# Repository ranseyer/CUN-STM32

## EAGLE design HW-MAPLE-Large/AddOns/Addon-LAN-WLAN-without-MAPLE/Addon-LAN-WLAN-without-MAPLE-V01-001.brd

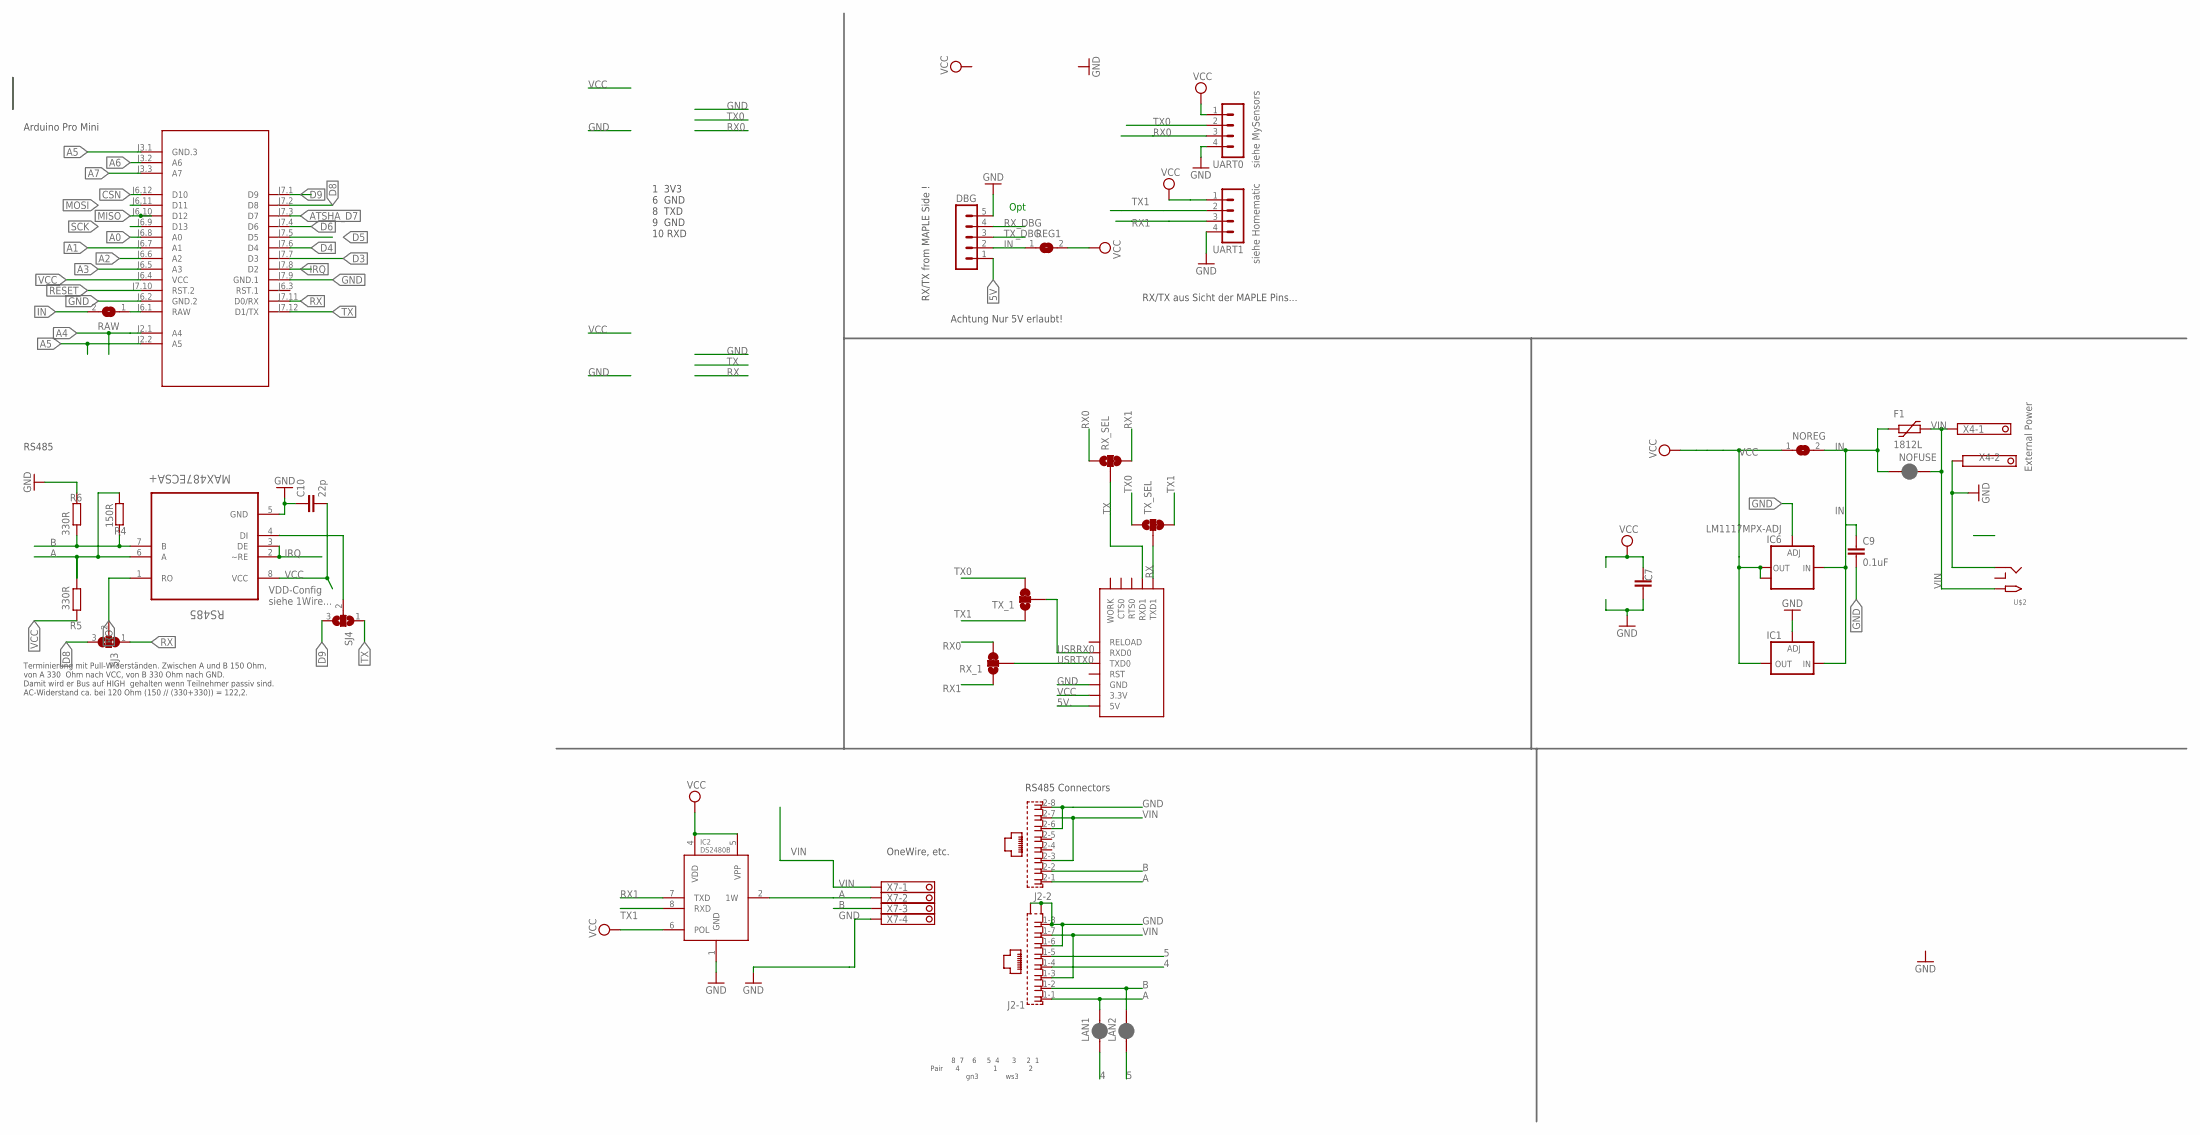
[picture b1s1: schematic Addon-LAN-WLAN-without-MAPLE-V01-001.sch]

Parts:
C7: C-EUC1812; C1812
C9: 0.1uF; C1206
C10: 22p; C0805
DBG: MA05-1
F1: 1812L
IC1: LD117ADT50TR; DPACK
IC2: DS2480B; SO08
IC6: LM1117MPX-ADJ; SOT223
J2: RJ45_2X_S
LAN1, LAN2: JUMPER-SMT_2_NC_PASTE_SILK; SMT-JUMPER_2_NC_PASTE_SILK
M1: ARDUINO-PRO-MINI-3.3V#NP; ARDUINO-PRO-MINI#NP
NOFUSE: JUMPER-SMT_2_NC_PASTE_NO-SILK; SMT-JUMPER_2_NC_PASTE_NO-SILK
NOREG: SJ
R4: 150R; R0805
R5, R6: 330R; R0805
RAW: SJ
REG1: SJ
RS485: MAX487ECSA+; SOIC127P600X175-8N
RX_1: JUMPER-SMT_3_1-NC_TRACE_SILK; SMT-JUMPER_3_1-NC_TRACE_SILK
RX_SEL: JUMPER-SMT_3_1-NC_TRACE_SILK; SMT-JUMPER_3_1-NC_TRACE_SILK
SJ3, SJ4: SJ2W; SJ_2
TX_1: JUMPER-SMT_3_1-NC_TRACE_SILK; SMT-JUMPER_3_1-NC_TRACE_SILK
TX_SEL: JUMPER-SMT_3_1-NC_TRACE_SILK; SMT-JUMPER_3_1-NC_TRACE_SILK
U$2: 2.1MMJACKTHM; PJ-102A
U$5: USR-TCP232-E2
UART0, UART1: MA04-1
X4: 1751248
X7: 1751264

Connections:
4: J2.1-4 (4), LAN1.1
5: J2.1-5 (5), LAN2.1
5V: DBG.1
5V.: U$5.5V
A: IC2.2 (1W), J2.1-1 (1), J2.2-1 (1), LAN1.2, R4.1, R5.2, RS485.6 (A), X7.2
A0: M1.J6.8 (A0)
A1: M1.J6.7 (A1)
A2: M1.J6.6 (A2)
A3: M1.J6.5 (A3)
A4: M1.J2.1 (A4)
A5: M1.J2.2 (A5), M1.J3.1 (GND.3)
A6: M1.J3.2 (A6)
A7: M1.J3.3 (A7)
ATSHA_D7: M1.J7.3 (D7)
B: J2.1-2 (2), J2.2-2 (2), LAN2.2, R4.2, R6.1, RS485.7 (B), X7.3
CSN: M1.J6.12 (D10)
D3: M1.J7.7 (D3)
D4: M1.J7.6 (D4)
D5: M1.J7.5 (D5)
D6: M1.J7.4 (D6)
D8: M1.J7.2 (D8), SJ3.3
D9: M1.J7.1 (D9), SJ4.3
DI1: RS485.4 (DI), SJ4.2
GND: C7.1, C9.2, C10.1, DBG.5, IC1.1 (ADJ), IC2.1 (GND), IC6.1 (ADJ), J2.1-6 (6), J2.1-8 (8), J2.2-6 (6), J2.2-8 (8), J2.G1 (S2), J2.G3 (S1), M1.J6.2 (GND.2), M1.J7.9 (GND.1), R6.2, RS485.5 (GND), U$2.RING, U$5.GND, UART0.4, UART1.4, X4.2, X7.4
IN: C9.1, DBG.2, F1.P$1 (1), IC1.3 (IN), IC6.3 (IN), NOFUSE.1, NOREG.2, RAW.2, REG1.1
IRQ: M1.J7.8 (D2), RS485.2 (~RE), RS485.3 (DE)
MISO: M1.J6.10 (D12)
MOSI: M1.J6.11 (D11)
RAW1: M1.J6.1 (RAW), RAW.1
RESET: M1.J7.10 (RST.2)
RO: RS485.1 (RO), SJ3.2
RX: M1.J7.11 (D0/RX), SJ3.1, TX_SEL.2, U$5.TXD1
RX0: RX_1.3, RX_SEL.1, UART0.3
RX1: IC2.7 (TXD), RX_1.1, RX_SEL.3, UART1.3
RX_DBG: DBG.4
SCK: M1.J6.9 (D13)
TX: M1.J7.12 (D1/TX), RX_SEL.2, SJ4.1, U$5.RXD1
TX0: TX_1.3, TX_SEL.1, UART0.2
TX1: IC2.8 (RXD), TX_1.1, TX_SEL.3, UART1.2
TX_DBG: DBG.3
USRRX0: TX_1.2, U$5.RXD0
USRTX0: RX_1.2, U$5.TXD0
VCC: C7.2, C10.2, IC1.4 (OUT), IC2.4 (VDD), IC2.5 (VPP), IC2.6 (POL), IC6.2 (OUT), IC6.TAB (OUT1), M1.J6.4 (VCC), NOREG.1, R5.1, REG1.2, RS485.8 (VCC), U$5.3.3V, UART0.1, UART1.1
VIN: F1.P$2 (2), J2.1-3 (3), J2.1-7 (7), J2.2-3 (3), J2.2-7 (7), NOFUSE.2, U$2.TIP, X4.1, X7.1

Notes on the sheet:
Opt
siehe Homematic
siehe MySensors
1 3V3 6 GND 8 TXD 9 GND 10 RXD
RX/TX from MAPLE Side !
External Power
RX/TX aus Sicht der MAPLE Pins...
Achtung Nur 5V erlaubt!
8 7 6 5 4 3 2 1 Pair 4 1 2 gn3 ws3
RS485 Connectors
OneWire, etc.
Arduino Pro Mini
RS485
VDD-Config siehe 1Wire...
Terminierung mit Pull-Widerständen. Zwischen A und B 150 Ohm, von A 330 Ohm nach VCC, von B 330 Ohm nach GND. Damit wird er Bus auf HIGH gehalten wenn Teilnehmer passiv sind. AC-Widerstand ca. bei 120 Ohm (150 // (330+330)) = 122,2.

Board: 2 copper layers, 32 parts (9 on the bottom side), 23 nets, no tracks yet.

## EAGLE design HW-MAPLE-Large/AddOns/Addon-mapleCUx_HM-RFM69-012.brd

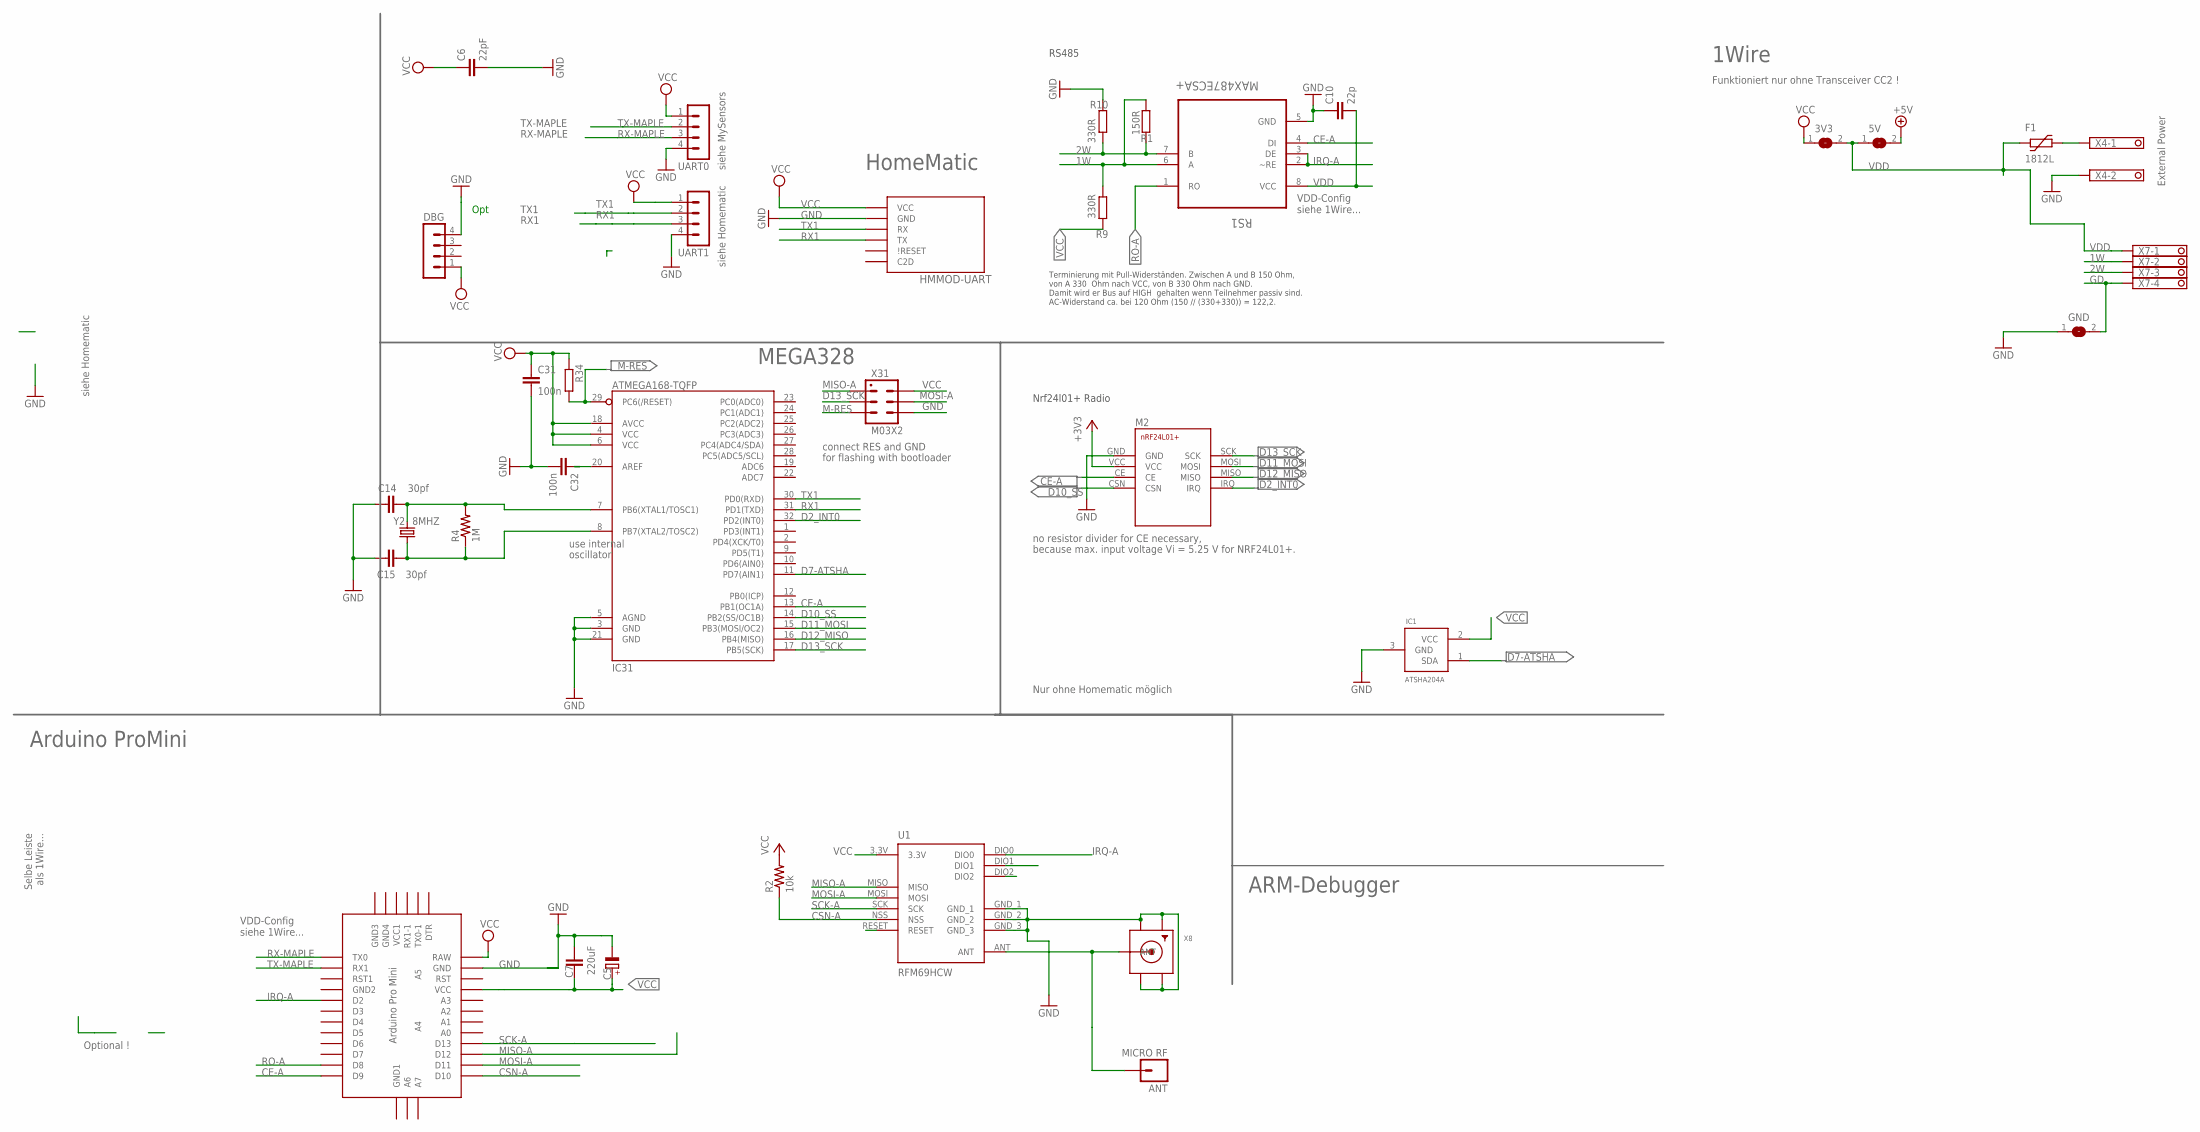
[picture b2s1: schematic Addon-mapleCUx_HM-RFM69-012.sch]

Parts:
3V3, 5V: SJ
ANT: MICRO RF; 1X01
C5: 220uF; E5-8,5
C6: 22pF; C0805
C7: C-EUC1812; C1812
C10: 22p; C0805
C14, C15: 30pf; 0805
C31, C32: 100n; C0805
DBG: MA04-1
F1: 1812L
GND: SJ
HMMOD-UART: HM-MOD-UARTDIL; HM-MOD-UART-DIL
IC1: ATSHA204A; SOT23
IC31: ATMEGA168-TQFP; TQFP32-08
M2: NRF24L01+SMD
R1: 150R; R0805
R2: 10k; 0805
R4: 1M; 0805
R9, R10: 330R; R0805
R34: R-EU_R0805; R0805
RS1: MAX487ECSA+; SOIC127P600X175-8N
U1: RFM69HCW; RFM69HCW-XXXS2
U$2: ABK-PRO-MINI
UART0, UART1: MA04-1
X4: 1751248
X7: 1751264
X8: SMACONNECTOR_EDGE; SMA_EDGELAUNCH
X31: M03X2; 2X03-1.27MM_SMD
Y2: 8MHZ; CRYSTAL-TXC-7A

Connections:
1W: R1.1, R9.2, RS1.6 (A), X7.2
2W: R1.2, R10.1, RS1.7 (B), X7.3
3.3V: M2.VCC
+5V: 5V.2
ANT: ANT.1, U1.ANT, X8.P (ANT)
CE-A: IC31.13 (PB1(OC1A)), M2.CE, RS1.4 (DI), U$2.D9
CSN-A: R2.1, U1.NSS, U$2.D10
D2_INT0: IC31.32 (PD2(INT0)), M2.IRQ
D7-ATSHA: IC1.1 (SDA), IC31.11 (PD7(AIN1))
D10_SS: IC31.14 (PB2(SS/OC1B)), M2.CSN
D11_MOSI: IC31.15 (PB3(MOSI/OC2)), M2.MOSI
D12_MISO: IC31.16 (PB4(MISO)), M2.MISO
D13_SCK: IC31.17 (PB5(SCK)), M2.SCK, X31.P$3 (3)
GD: GND.2, X7.4
GND: C5.-, C6.2, C7.1, C10.1, C14.1, C15.1, C31.2, C32.2, DBG.4, GND.1, HMMOD-UART.2 (GND), IC1.3 (GND), IC31.3 (GND), IC31.5 (AGND), IC31.21 (GND), M2.GND, R10.2, RS1.5 (GND), U1.GND_1, U1.GND_2, U1.GND_3, U$2.GND, UART0.4, UART1.4, X4.2, X8.GND@1 (GND4), X8.GND@2 (GND3), X8.GND@3 (GND2), X8.GND@4 (GND1), X31.P$6 (6)
IRQ-A: RS1.2 (~RE), RS1.3 (DE), U1.DIO0, U$2.D2
M-RES: IC31.29 (PC6(/RESET)), R34.2, X31.P$5 (5)
MISO-A: U1.MISO, U$2.D12, X31.P$1 (1)
MOSI-A: U1.MOSI, U$2.D11, X31.P$4 (4)
unnamed: C14.2, IC31.7 (PB6(XTAL1/TOSC1)), R4.2, Y2.P$2 (2)
unnamed: C32.1, IC31.20 (AREF)
unnamed: C15.2, IC31.8 (PB7(XTAL2/TOSC2)), R4.1, Y2.P$1 (1)
unnamed: F1.P$2 (2), X4.1
RO-A: RS1.1 (RO), U$2.D8
RX1: HMMOD-UART.5 (TX), IC31.31 (PD1(TXD)), UART1.3
RX-MAPLE: U$2.TX0, UART0.3
SCK-A: U1.SCK, U$2.D13
TX1: HMMOD-UART.6 (RX), IC31.30 (PD0(RXD)), UART1.2
TX-MAPLE: U$2.RX1, UART0.2
VCC: 3V3.1, C5.+, C6.1, C7.2, C31.1, DBG.1, HMMOD-UART.1 (VCC), IC1.2 (VCC), IC31.4 (VCC), IC31.6 (VCC), IC31.18 (AVCC), R2.2, R9.1, R34.1, U1.3.3V, U$2.RAW, U$2.VCC, UART0.1, UART1.1, X31.P$2 (2)
VDD: 3V3.2, 5V.1, C10.2, F1.P$1 (1), RS1.8 (VCC), X7.1

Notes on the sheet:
Opt
siehe Homematic
siehe MySensors
HomeMatic
Arduino ProMini
MEGA328
ARM-Debugger
Selbe Leiste als 1Wire...
VDD-Config siehe 1Wire...
Optional !
use internal
oscillator
connect RES and GND
for flashing with bootloader
Nrf24l01+ Radio
no resistor divider for CE necessary,
because max. input voltage Vi = 5.25 V for NRF24L01+.
Nur ohne Homematic möglich
RS485
Terminierung mit Pull-Widerständen. Zwischen A und B 150 Ohm, von A 330 Ohm nach VCC, von B 330 Ohm nach GND. Damit wird er Bus auf HIGH gehalten wenn Teilnehmer passiv sind. AC-Widerstand ca. bei 120 Ohm (150 // (330+330)) = 122,2.
1Wire
External Power
Funktioniert nur ohne Transceiver CC2 !

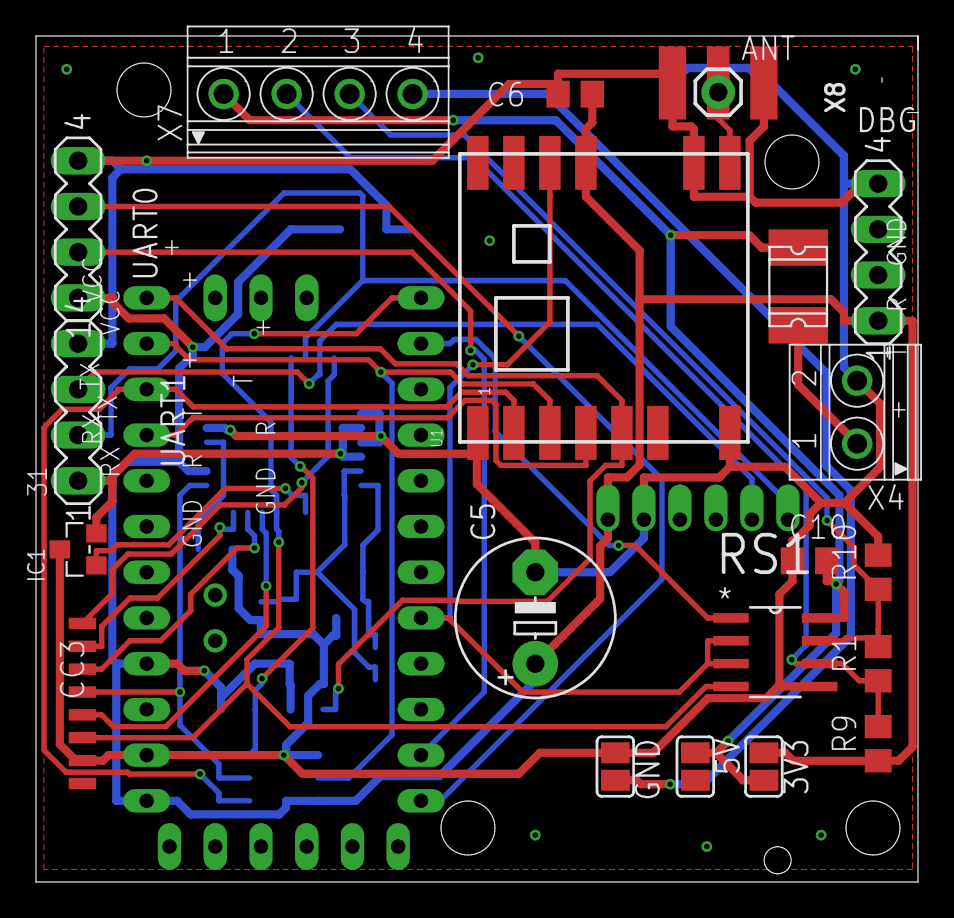
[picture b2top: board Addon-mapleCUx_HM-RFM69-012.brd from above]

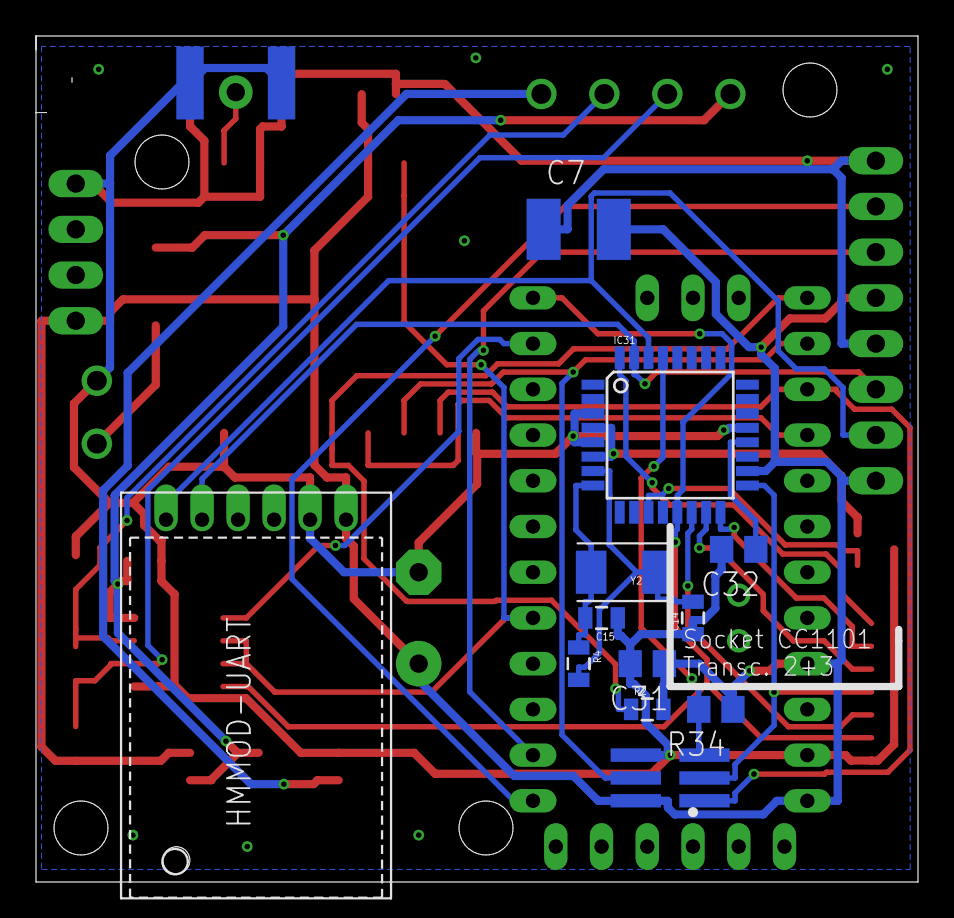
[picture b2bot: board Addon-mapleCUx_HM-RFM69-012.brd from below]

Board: 2 copper layers, 49.0 x 47.0 mm, 34 parts (12 on the bottom side), 29 nets.

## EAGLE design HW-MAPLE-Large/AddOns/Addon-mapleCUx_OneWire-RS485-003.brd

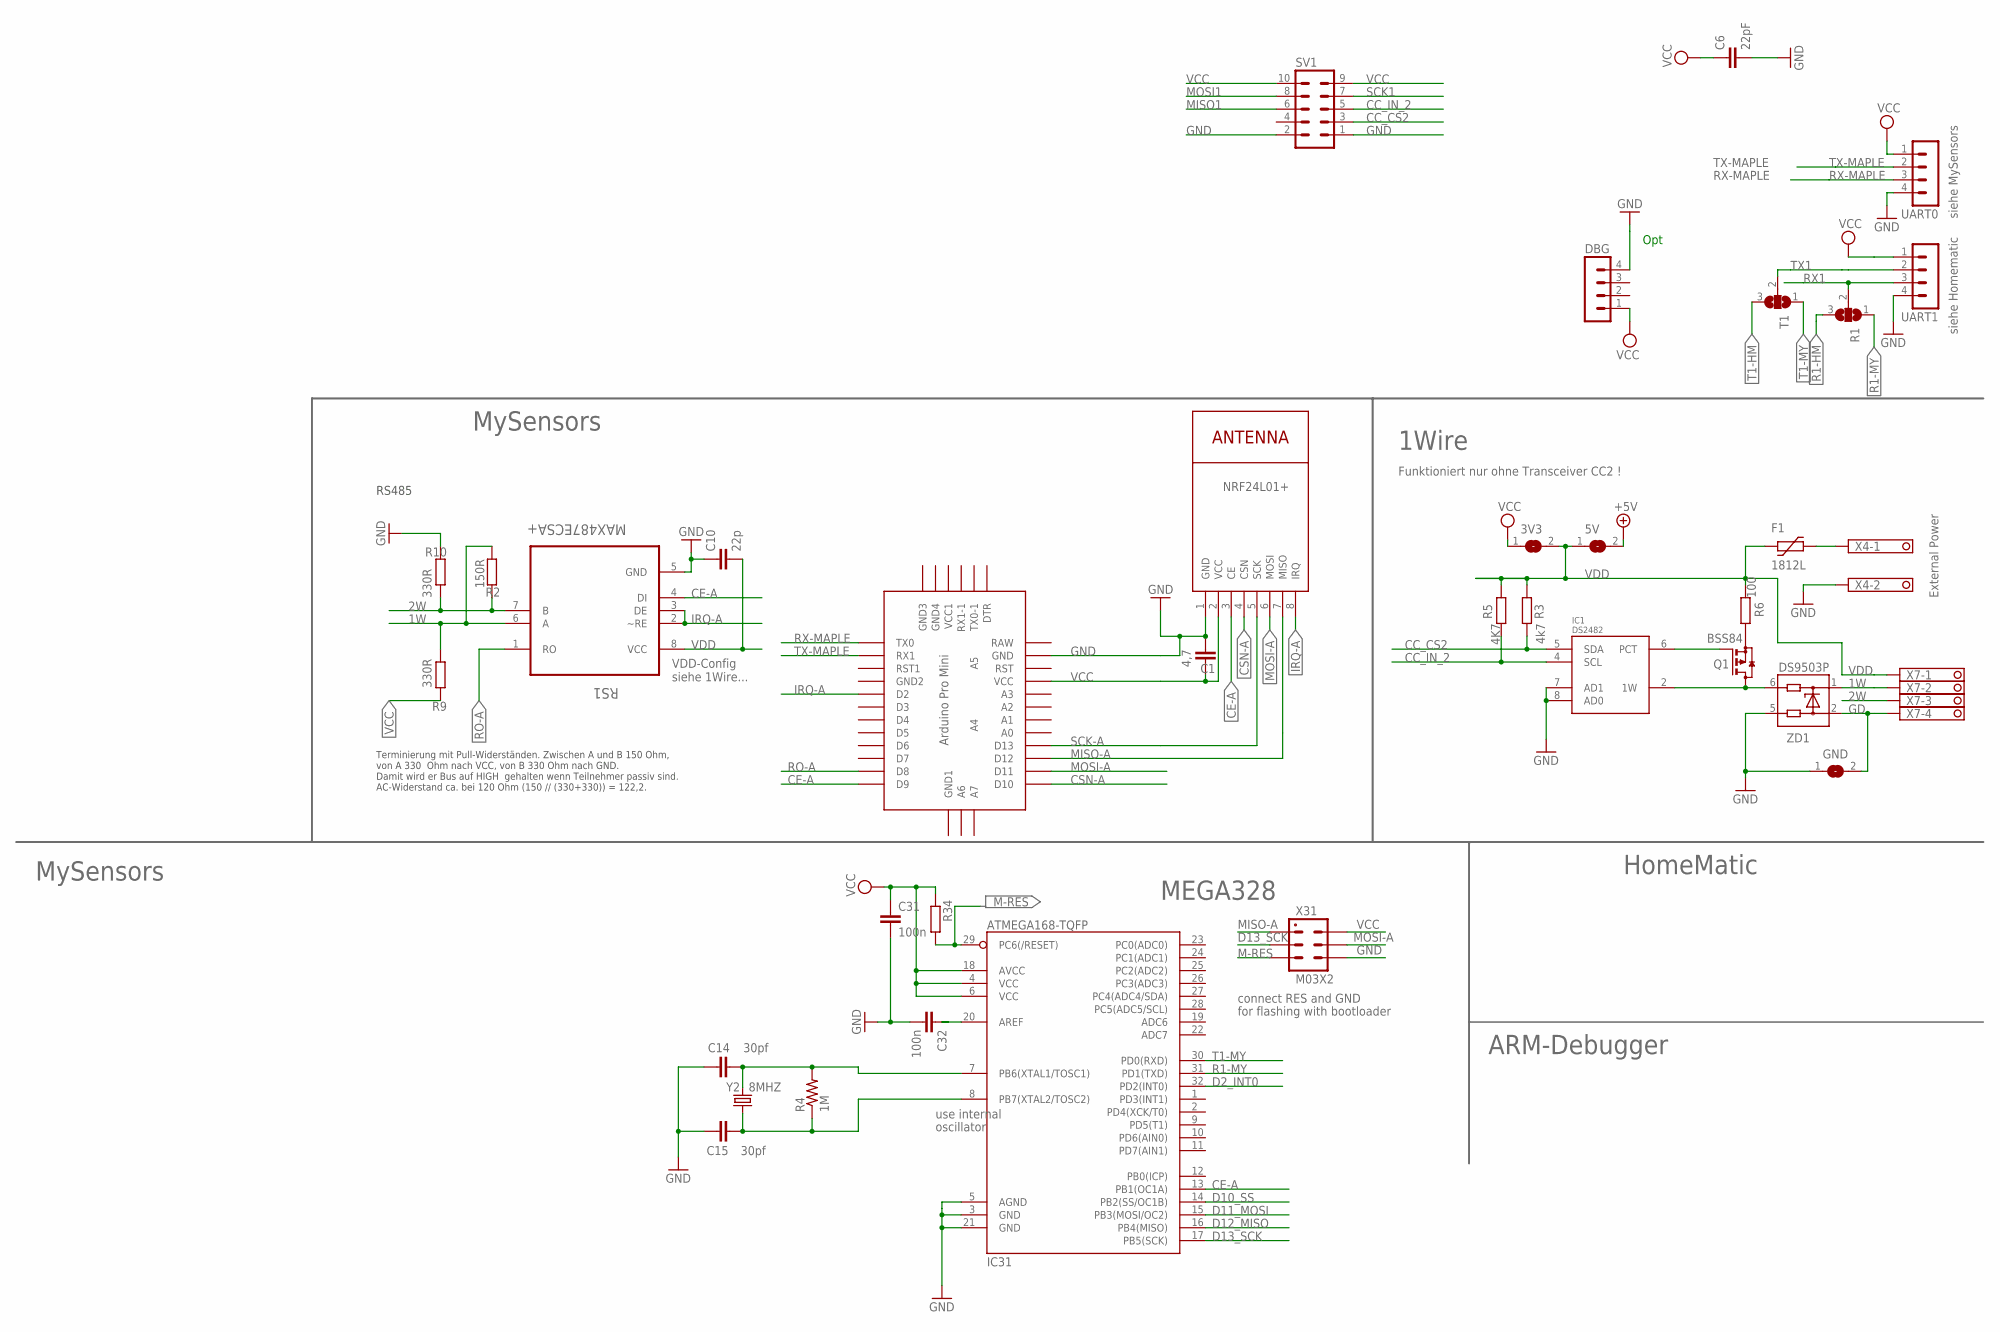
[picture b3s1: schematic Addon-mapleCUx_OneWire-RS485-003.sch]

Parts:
3V3, 5V: SJ
C1: 4,7; C1210
C6: 22pF; C0805
C10: 22p; C0805
C14, C15: 30pf; 0805
C31, C32: 100n; C0805
DBG: MA04-1
F1: 1812L
GND: SJ
IC1: DS2482; SO08
IC31: ATMEGA168-TQFP; TQFP32-08
NRF24L01+: NRF24L01+; WIRELESS-NRF24L01
Q1: BSS84; SOT23
R1: SJ2W; SJ_2
R2: 150R; R0805
R3: 4k7; R0805
R4: 1M; 0805
R5: 4K7; R0805
R6: 100; R0805
R9, R10: 330R; R0805
R34: R-EU_R0805; R0805
RS1: MAX487ECSA+; SOIC127P600X175-8N
SV1: MA05-2
T1: SJ2W; SJ_2
U$1: ABK-PRO-MINI
UART0, UART1: MA04-1
X4: 1751248
X7: 1751264
X31: M03X2; 2X03-1.27MM_SMD
Y2: 8MHZ; CRYSTAL-TXC-7A
ZD1: DS9503P; TSOC6

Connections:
1W: R2.1, R9.2, RS1.6 (A), X7.2, ZD1.1
2W: R2.2, R10.1, RS1.7 (B), X7.3
+5V: 5V.2
CC_CS2: IC1.5 (SDA), R3.2, SV1.3
CC_IN_2: IC1.4 (SCL), R5.2, SV1.5
CE-A: IC31.13 (PB1(OC1A)), NRF24L01+.3 (CE), RS1.4 (DI), U$1.D9
CSN-A: NRF24L01+.4 (CSN), U$1.D10
D2_INT0: IC31.32 (PD2(INT0))
D10_SS: IC31.14 (PB2(SS/OC1B))
D11_MOSI: IC31.15 (PB3(MOSI/OC2))
D12_MISO: IC31.16 (PB4(MISO))
D13_SCK: IC31.17 (PB5(SCK)), X31.P$3 (3)
GD: GND.2, X7.4, ZD1.2
GND: C1.1, C6.2, C10.1, C14.1, C15.1, C31.2, C32.2, DBG.4, GND.1, IC1.3 (GND), IC1.7 (AD1), IC1.8 (AD0), IC31.3 (GND), IC31.5 (AGND), IC31.21 (GND), NRF24L01+.1 (GND), R10.2, RS1.5 (GND), SV1.1, SV1.2, U$1.GND, UART0.4, UART1.4, X4.2, X31.P$6 (6), ZD1.5
IRQ-A: NRF24L01+.8 (IRQ), RS1.2 (~RE), RS1.3 (DE), U$1.D2
M-RES: IC31.29 (PC6(/RESET)), R34.2, X31.P$5 (5)
MISO1: SV1.6
MISO-A: NRF24L01+.7 (MISO), U$1.D12, X31.P$1 (1)
MOSI1: SV1.8
MOSI-A: NRF24L01+.6 (MOSI), U$1.D11, X31.P$4 (4)
unnamed: C14.2, IC31.7 (PB6(XTAL1/TOSC1)), R4.2, Y2.P$2 (2)
unnamed: C32.1, IC31.20 (AREF)
unnamed: C15.2, IC31.8 (PB7(XTAL2/TOSC2)), R4.1, Y2.P$1 (1)
unnamed: F1.P$2 (2), X4.1
unnamed: IC1.6 (PCT), Q1.1 (G)
unnamed: IC1.2 (1W), Q1.3 (D), ZD1.6
unnamed: Q1.2 (S), R6.1
R1-HM: R1.3
R1-MY: IC31.31 (PD1(TXD)), R1.1
RO-A: RS1.1 (RO), U$1.D8
RX1: R1.2, UART1.3
RX-MAPLE: U$1.TX0, UART0.3
SCK1: SV1.7
SCK-A: NRF24L01+.5 (SCK), U$1.D13
T1-HM: T1.3
T1-MY: IC31.30 (PD0(RXD)), T1.1
TX1: T1.2, UART1.2
TX-MAPLE: U$1.RX1, UART0.2
VCC: 3V3.1, C1.2, C6.1, C31.1, DBG.1, IC31.4 (VCC), IC31.6 (VCC), IC31.18 (AVCC), NRF24L01+.2 (VCC), R9.1, R34.1, SV1.9, SV1.10, U$1.VCC, UART0.1, UART1.1, X31.P$2 (2)
VDD: 3V3.2, 5V.1, C10.2, F1.P$1 (1), IC1.1 (VDD), R3.1, R5.1, R6.2, RS1.8 (VCC), X7.1

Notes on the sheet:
Opt
siehe Homematic
siehe MySensors
MySensors
HomeMatic
ARM-Debugger
MEGA328
use internal
oscillator
connect RES and GND
for flashing with bootloader
1Wire
External Power
Funktioniert nur ohne Transceiver CC2 !
RS485
VDD-Config siehe 1Wire...
Terminierung mit Pull-Widerständen. Zwischen A und B 150 Ohm, von A 330 Ohm nach VCC, von B 330 Ohm nach GND. Damit wird er Bus auf HIGH gehalten wenn Teilnehmer passiv sind. AC-Widerstand ca. bei 120 Ohm (150 // (330+330)) = 122,2.

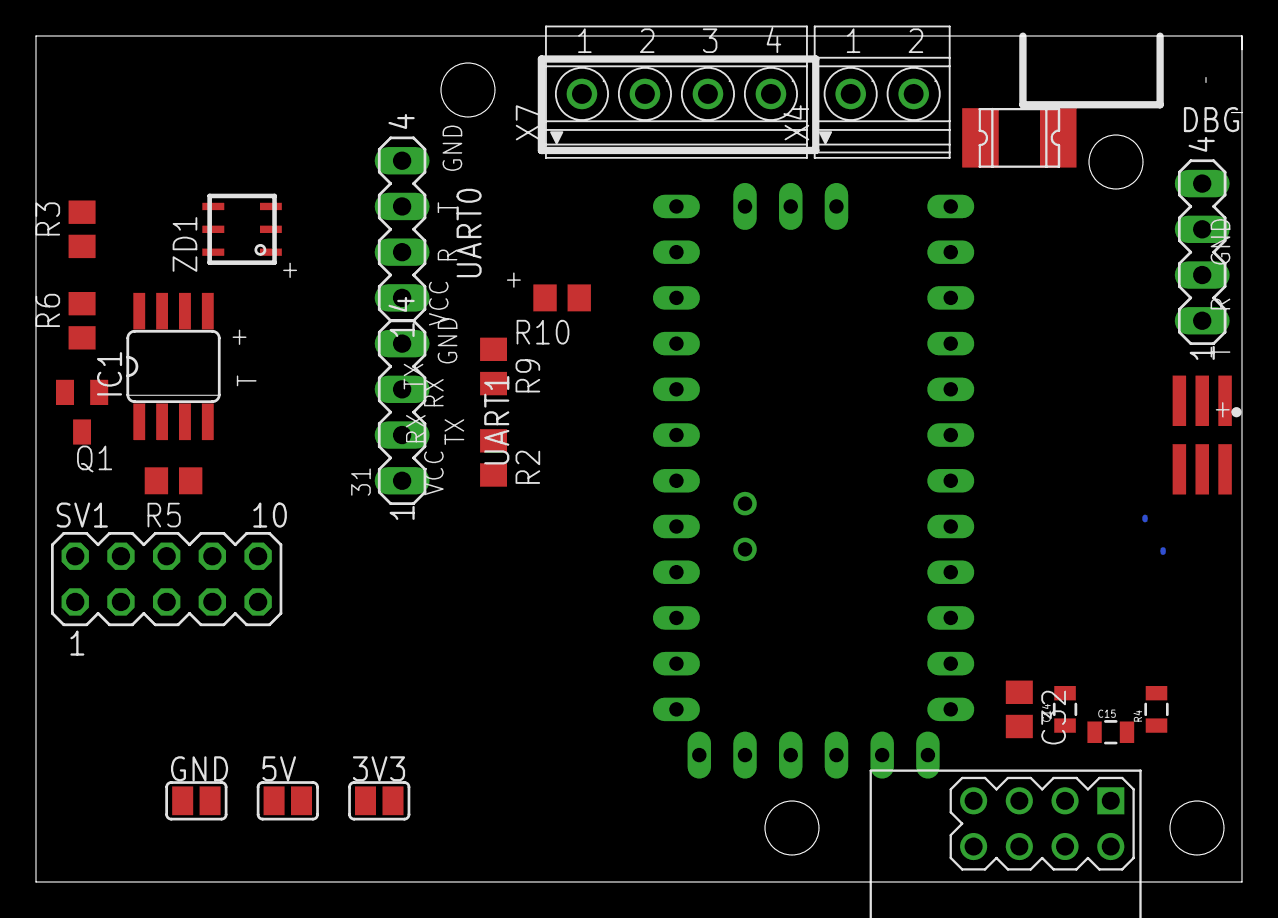
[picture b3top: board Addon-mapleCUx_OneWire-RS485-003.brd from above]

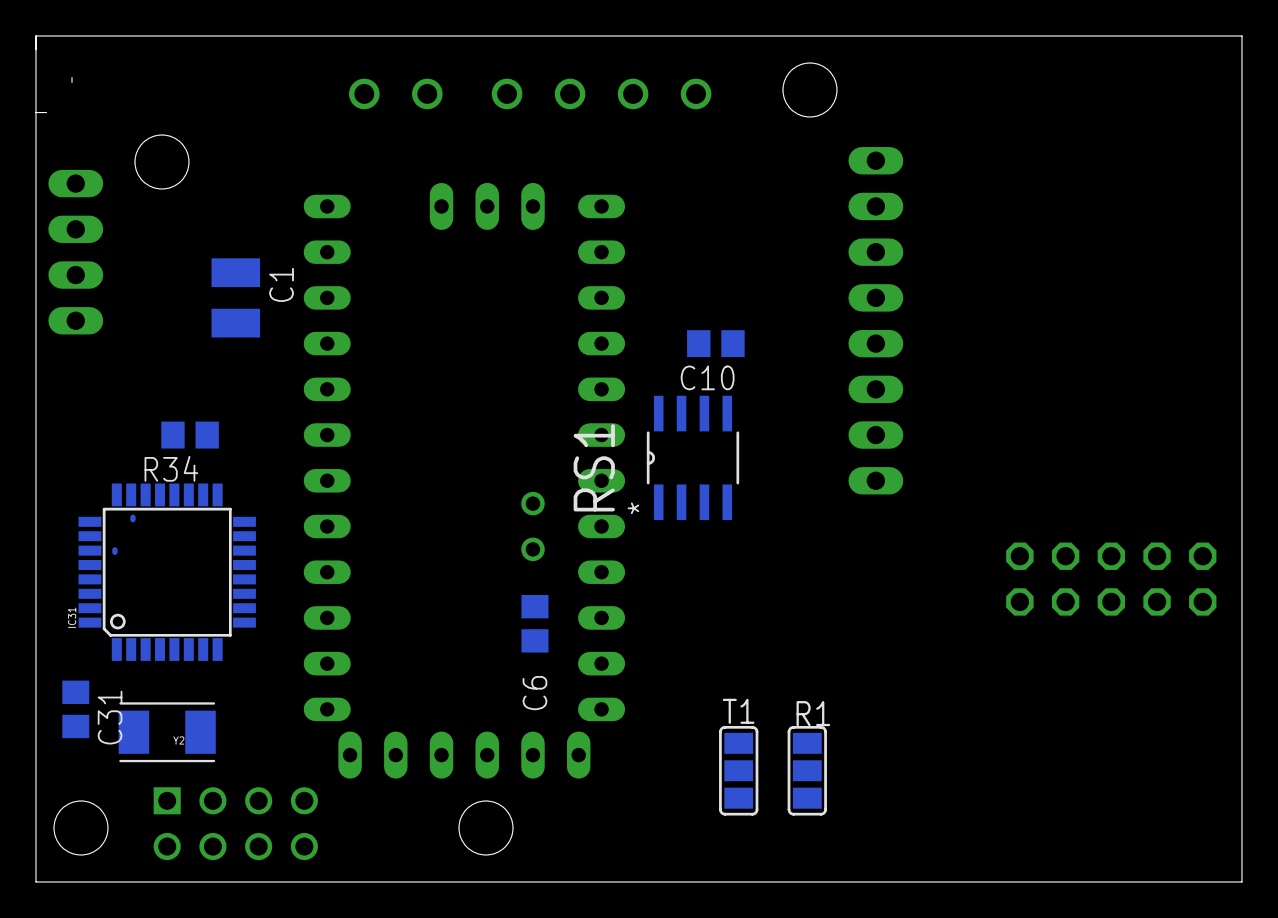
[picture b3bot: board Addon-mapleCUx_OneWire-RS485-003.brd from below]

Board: 2 copper layers, 67.0 x 47.0 mm, 36 parts (10 on the bottom side), 30 nets.

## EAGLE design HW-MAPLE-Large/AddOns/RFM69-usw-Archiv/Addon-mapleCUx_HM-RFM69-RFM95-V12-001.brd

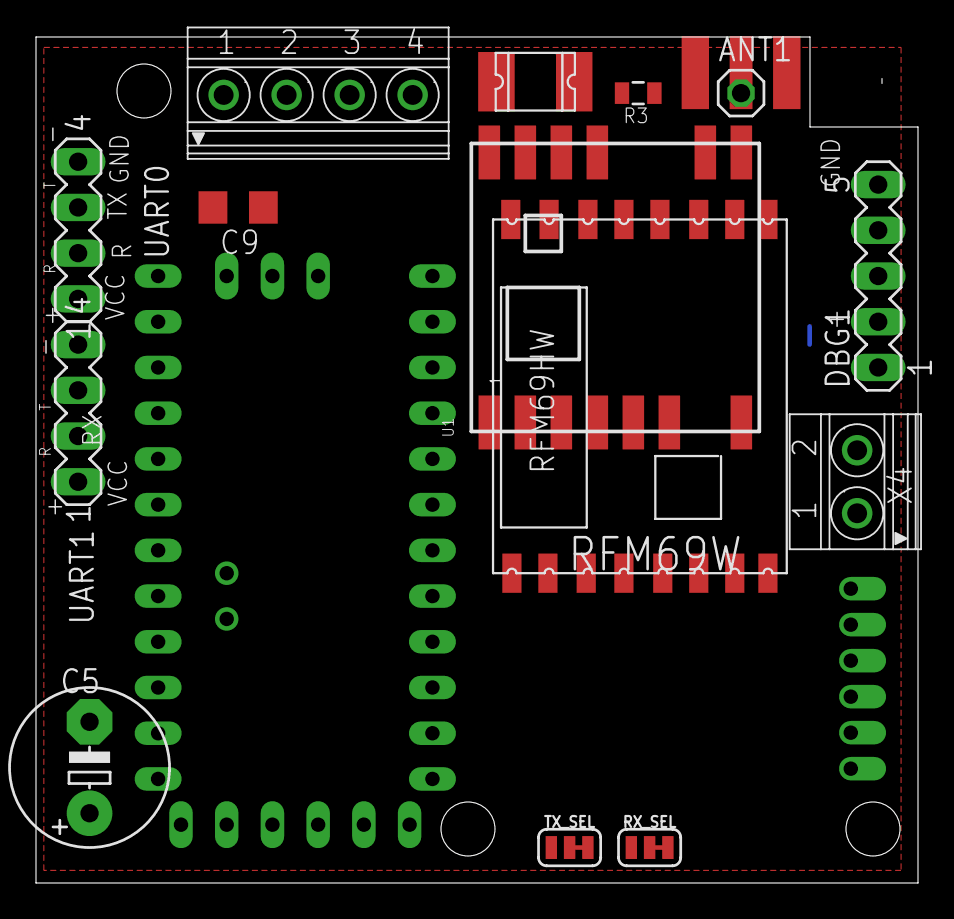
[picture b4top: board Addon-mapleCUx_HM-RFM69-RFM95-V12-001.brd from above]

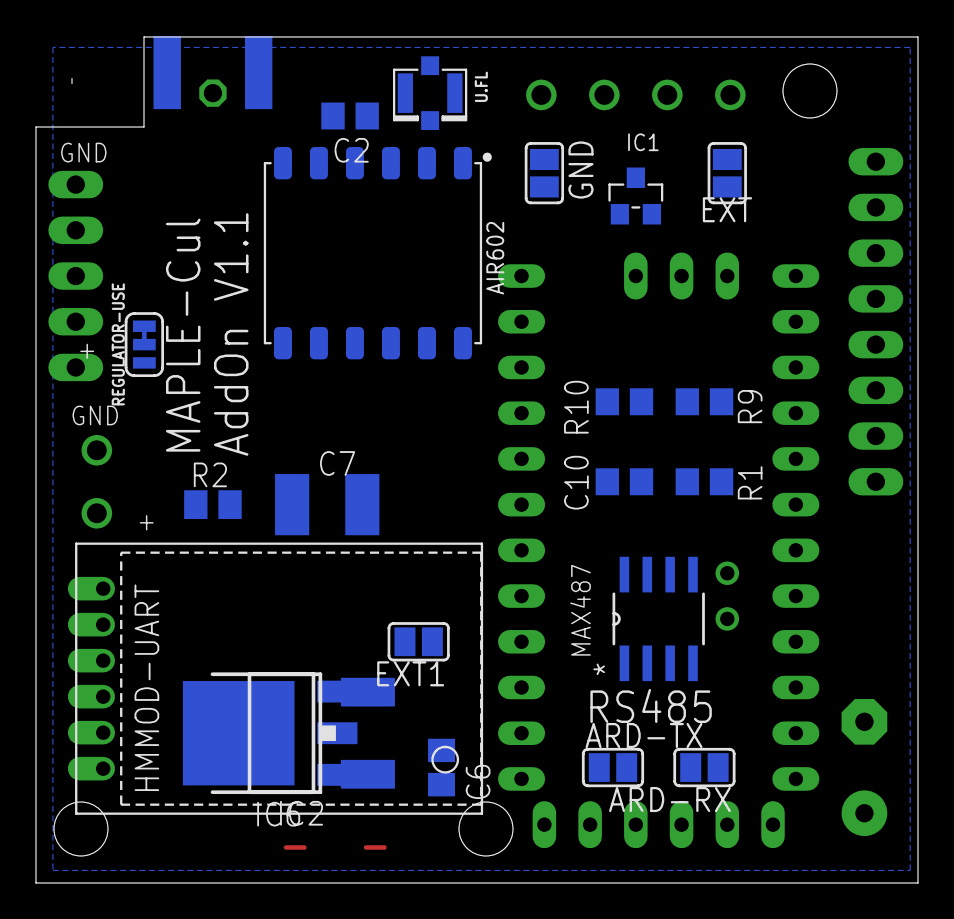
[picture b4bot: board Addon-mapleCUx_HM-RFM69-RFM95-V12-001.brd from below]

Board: 2 copper layers, 49.0 x 47.0 mm, 37 parts (21 on the bottom side), 27 nets, no tracks yet.

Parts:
AIR602: MODULE12P-2.0-10X12MM
ANT1: 1X01
ARD-RX: SJ
ARD-TX: SJ
C2, C6: 22pF; C0805
C5: 220uF; E5-8,5
C7: C1812
C9: 0.1uF; C1206
C10: 22p; C0805
DBG1: MA05-1
EXT, EXT1: SJ
F1: 1812L
GND: SJ
HMMOD-UART: HM-MOD-UARTDIL; HM-MOD-UART-DIL
IC1: ATSHA204A; SOT23
IC2: LD117ADT50TR; DPACK
IC6: LM1117MPX-ADJ; SOT223
R1: 150R; R0805
R2: 10k; M0805
R3: 10k; 0805
R9, R10: 330R; R0805
REGULATOR-USE: JUMPER-SMT_3_1-NC_TRACE_SILK; SMT-JUMPER_3_1-NC_TRACE_SILK
RFM69W: RFM69HW; RFM
RS1: MAX487ECSA+; SOIC127P600X175-8N
RX_SEL: JUMPER-SMT_3_1-NC_TRACE_SILK; SMT-JUMPER_3_1-NC_TRACE_SILK
TX_SEL: JUMPER-SMT_3_1-NC_TRACE_SILK; SMT-JUMPER_3_1-NC_TRACE_SILK
U1: RFM69HCW; RFM69HCW-XXXS2
U$2: ABK-PRO-MINI
U.FL: U.FL
UART0, UART1: MA04-1
X2: SMA_EDGELAUNCH
X4: 1751248
X7: 1751264

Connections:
1W: R1.1, R9.2, RS1.6, X7.2
2W: R1.2, R10.1, RS1.7, X7.3
AN: AIR602.2, U.FL.FEED
ANT: ANT1.1, RFM69W.ANT, U1.ANT, X2.P
CE-A: RS1.4, U$2.D9
CSN-A: R2.1, R3.1, RFM69W.NSS, U1.NSS, U$2.D10
D7-ATSHA-ARDU: IC1.1, U$2.D7
EXT: EXT.2, F1.P$1, X7.1
GD: GND.2, X7.4
GND: AIR602.1, AIR602.3, C2.1, C5.-, C6.2, C7.1, C9.2, C10.1, DBG1.5, GND.1, HMMOD-UART.2, IC1.3, IC2.1, IC6.1, R10.2, RFM69W.GNDA, RFM69W.GNDB, RS1.5, U1.GND_1, U1.GND_2, U1.GND_3, U$2.GND, U.FL.1, U.FL.2, UART0.4, UART1.4, X2.GND@1, X2.GND@2, X2.GND@3, X2.GND@4, X4.2
IN: C9.1, DBG1.2, EXT.1, EXT1.2, IC2.3, IC6.3, REGULATOR-USE.3
IRQ-A: RFM69W.DIO0, RS1.2, RS1.3, U1.DIO0, U$2.D2
MISO-A: RFM69W.MISO, U1.MISO, U$2.D12
MOSI-A: RFM69W.MOSI, U1.MOSI, U$2.D11
unnamed: F1.P$2, X4.1
RO-A: RS1.1, U$2.D8
RX: ARD-RX.2, TX_SEL.2, U$2.RX1
RX0: RX_SEL.1, UART0.3
RX1: HMMOD-UART.5, RX_SEL.3, UART1.3
RX_DBG: AIR602.11, ARD-RX.1, DBG1.4
SCK-A: RFM69W.SCK, U1.SCK, U$2.D13
TX: ARD-TX.1, RX_SEL.2, U$2.TX0
TX0: TX_SEL.3, UART0.2
TX1: HMMOD-UART.6, TX_SEL.1, UART1.2
TX_DBG: AIR602.10, ARD-TX.2, DBG1.3
VCC: AIR602.4, C2.2, C5.+, C6.1, C7.2, EXT1.1, HMMOD-UART.1, IC1.2, IC2.4, IC6.2, IC6.TAB, R2.2, R3.2, R9.1, REGULATOR-USE.2, RFM69W.VCC, U1.3.3V, U$2.RAW, U$2.VCC, UART0.1, UART1.1
VDD: C10.2, RS1.8

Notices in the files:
parts and their libraries:
SparkFun-Jumpers: Licensing: Creative Commons ShareAlike 4.0 International - https://creativecommons.org/licenses/by-sa/4.0
diy-modules: Released under the Creative Commons Attribution 4.0 International License: http://creativecommons.org/licenses/by/4.0
